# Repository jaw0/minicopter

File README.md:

teeny-tiny autonomous quadcopter flying machine

* 25mm square (smaller than one inch!)

* STM32F4 - ARM Cortex-M4

* 10 DOF IMU
  * accelerometer
  * gyro
  * magnetometer
  * barometer

* 3D printed frame

* buggy, poorly performing software

* see also: [hackaday.io](https://hackaday.io/project/7947-quadcopter-in-one-inch)

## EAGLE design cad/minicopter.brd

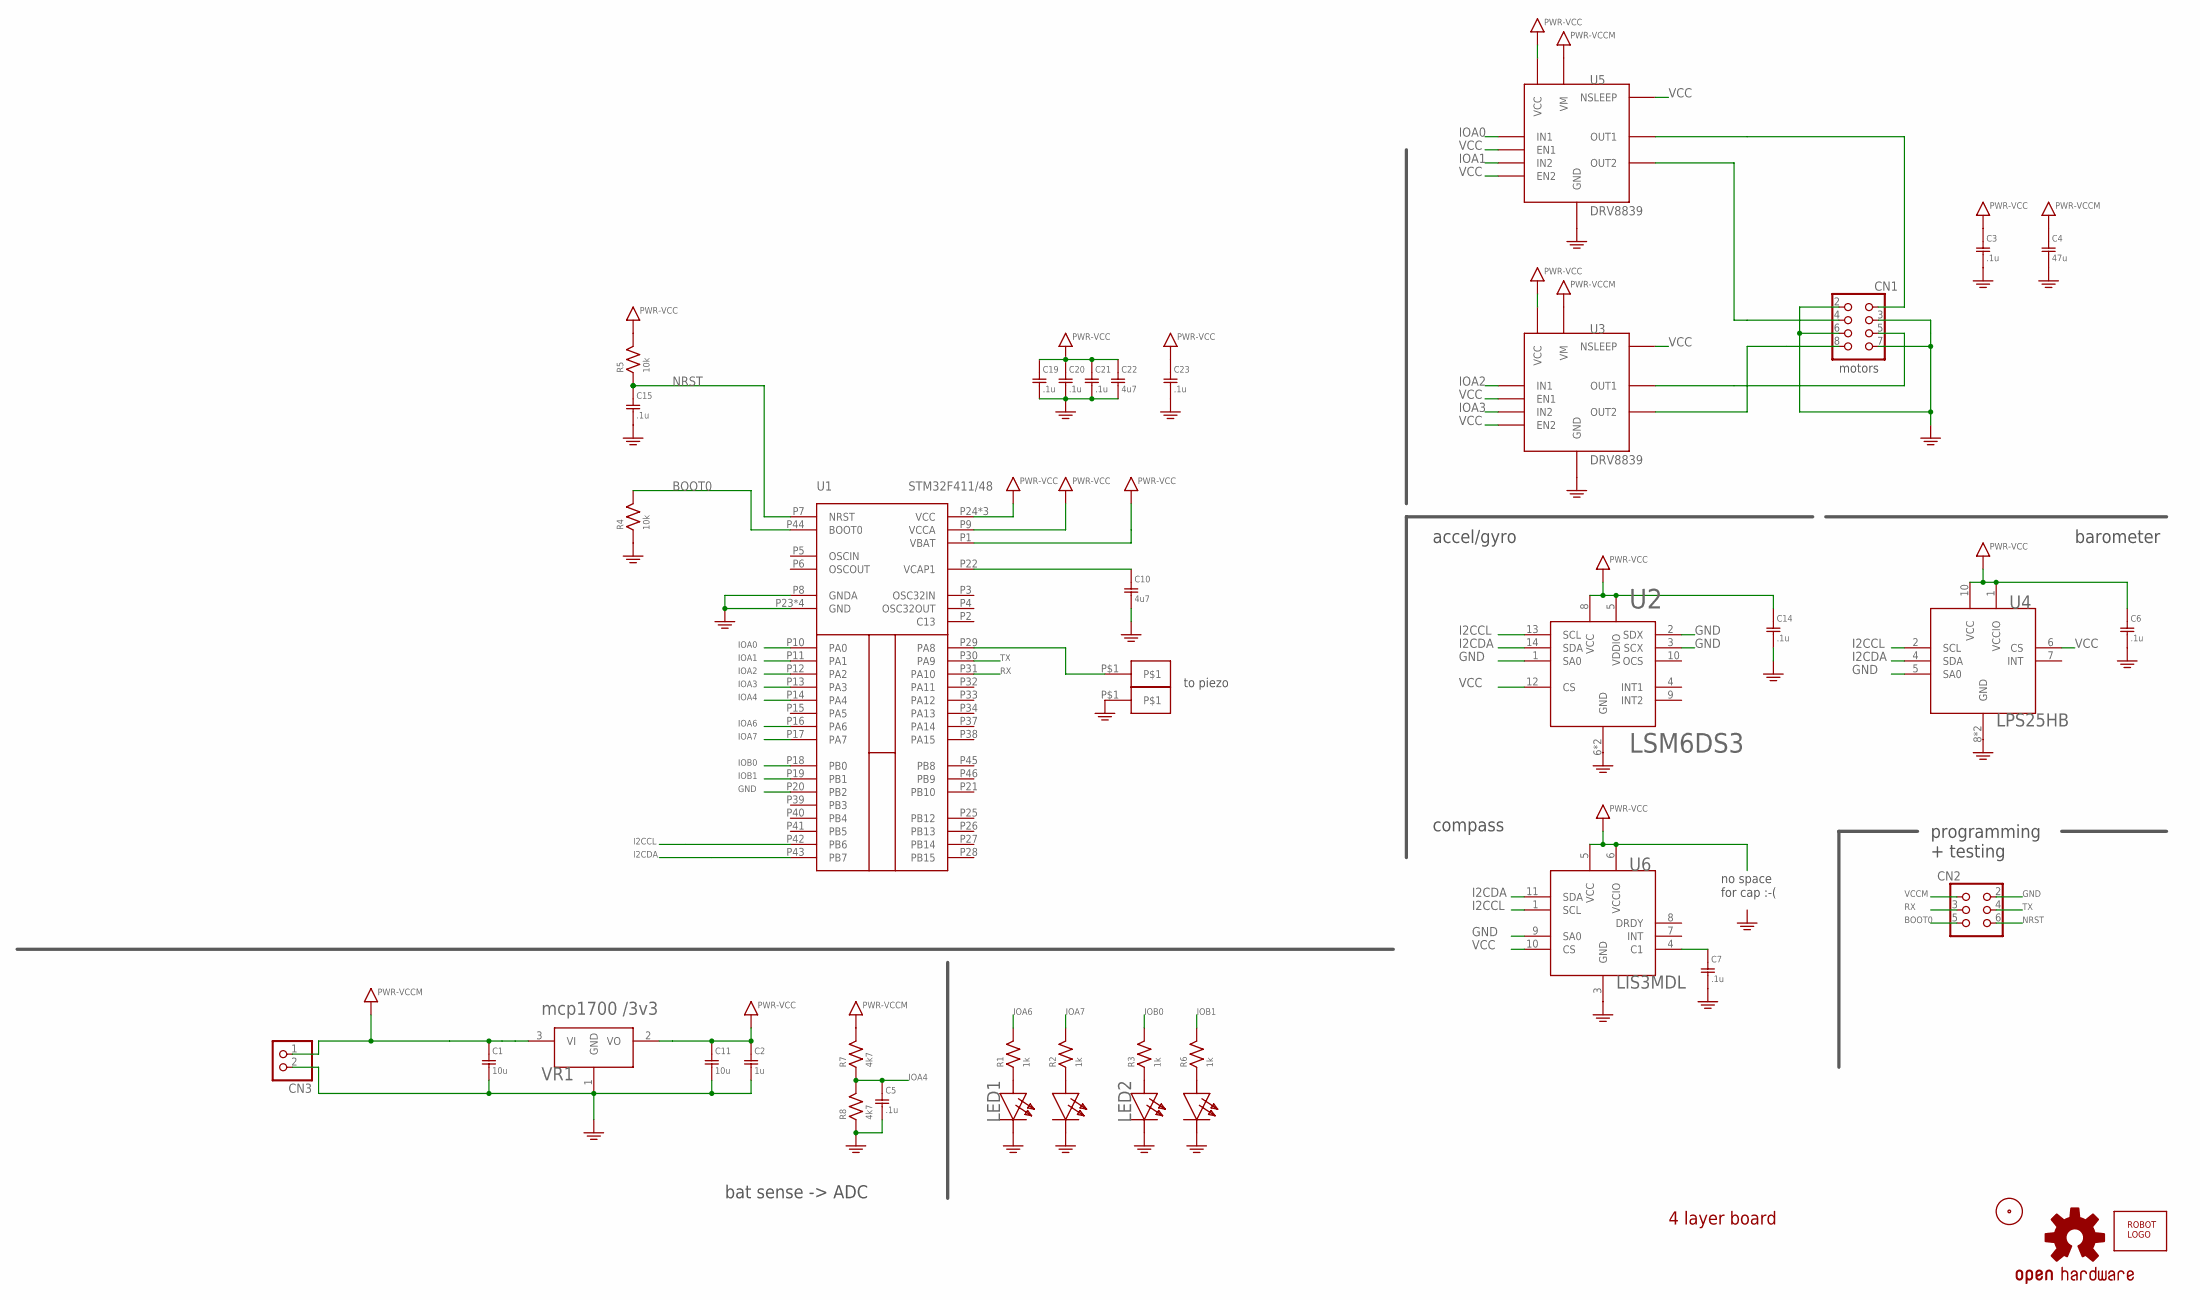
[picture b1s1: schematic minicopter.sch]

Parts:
C1, C11: 10u; SMD0603
C2: 1u; SMD0603
C3, C5, C6, C7, C14, C15, C19, C20, C21, C23: .1u; SMD0603
C4: 47u; SMD0805
C10, C22: 4u7; SMD0603
CN1: HEADER-2X4; HEADER-2X04-THM
CN2: HEADER-3X2-PTH
CN3: JST_2PIN-THM; JST-PH-2-THM
CN4, CN5: HEADER-1X1SMALL; HEADER-1X1-SMALL
LED1, LED2: LED-DUAL0805; SMD0805-DUAL
LOGO1: OSHW-LOGOM; OSHW-LOGO-M
R1, R2, R3, R6: 1k; SMD0603
R4, R5: 10k; SMD0603
R7, R8: 4k7; SMD0603
U1: STM32F411/48; UQPFN48
U2: LSM6DS3; LGA14A
U3, U5: DRV8839; WSON12
U4: LPS25HB; HLGA10L
U6: LIS3MDL; LGA12
U$1: ROBOTMAN-LOGO
U$2: FIDUCIAL
VR1: mcp1700 /3v3; SOT-23-3

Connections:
BOOT0: CN2.5, R4.2, U1.P44 (BOOT0)
GND: C1.2, C2.2, C3.2, C4.2, C5.2, C6.2, C7.2, C10.2, C11.2, C14.2, C15.2, C19.2, C20.2, C21.2, C22.2, C23.2, CN1.2, CN1.3, CN1.6, CN1.7, CN2.2, CN3.2 (1), CN5.P$1, LED1.2 (CB), LED1.3 (CR), LED2.2 (CB), LED2.3 (CR), R4.1, R8.1, U1.P8 (GNDA), U1.P20 (PB2), U1.P23 (GND), U1.P35 (GND), U1.P47 (GND), U1.PAD (GND), U2.1 (SA0), U2.2 (SDX), U2.3 (SCX), U2.6 (GND), U2.7 (GND), U3.5 (GND), U3.6 (GND), U3.GND3 (GND), U3.GND4 (GND), U3.GND5 (GND), U3.GND6 (GND), U3.GND7 (GND), U4.5 (SA0), U4.8 (GND), U4.9 (GND), U5.5 (GND), U5.6 (GND), U5.GND3 (GND), U5.GND4 (GND), U5.GND5 (GND), U5.GND6 (GND), U5.GND7 (GND), U6.3 (GND), U6.9 (SA0), VR1.1 (GND)
I2CCL: U1.P42 (PB6), U2.13 (SCL), U4.2 (SCL), U6.1 (SCL)
I2CDA: U1.P43 (PB7), U2.14 (SDA), U4.4 (SDA), U6.11 (SDA)
IOA0: U1.P10 (PA0), U5.10 (IN1)
IOA1: U1.P11 (PA1), U5.8 (IN2)
IOA2: U1.P12 (PA2), U3.10 (IN1)
IOA3: U1.P13 (PA3), U3.8 (IN2)
IOA4: C5.1, R7.1, R8.2, U1.P14 (PA4)
IOA6: R1.2, U1.P16 (PA6)
IOA7: R2.2, U1.P17 (PA7)
IOB0: R3.2, U1.P18 (PB0)
IOB1: R6.2, U1.P19 (PB1)
unnamed: LED1.1 (AB), R1.1
unnamed: LED1.4 (AR), R2.1
unnamed: LED2.1 (AB), R3.1
unnamed: LED2.4 (AR), R6.1
unnamed: CN1.1, U5.3 (OUT1)
unnamed: CN1.4, U5.4 (OUT2)
unnamed: C10.1, U1.P22 (VCAP1)
unnamed: CN1.5, U3.3 (OUT1)
unnamed: CN1.8, U3.4 (OUT2)
unnamed: C7.1, U6.4 (C1)
NRST: C15.1, CN2.6, R5.1, U1.P7 (NRST)
PZ0: CN4.P$1, U1.P29 (PA8)
RX: CN2.3, U1.P31 (PA10)
TX: CN2.4, U1.P30 (PA9)
VCC: C2.1, C3.1, C6.1, C11.1, C14.1, C19.1, C20.1, C21.1, C22.1, C23.1, R5.2, U1.P1 (VBAT), U1.P9 (VCCA), U1.P24 (VCC), U1.P36 (VCC), U1.P48 (VCC), U2.5 (VDDIO), U2.8 (VCC), U2.12 (CS), U3.7 (EN2), U3.9 (EN1), U3.11 (NSLEEP), U3.12 (VCC), U4.1 (VCCIO), U4.6 (CS), U4.10 (VCC), U5.7 (EN2), U5.9 (EN1), U5.11 (NSLEEP), U5.12 (VCC), U6.5 (VCC), U6.6 (VCCIO), U6.10 (CS), VR1.2 (VO)
VCCM: C1.1, C4.1, CN2.1, CN3.1 (2), R7.2, U3.1 (VM), U3.2 (VM), U5.1 (VM), U5.2 (VM), VR1.3 (VI)

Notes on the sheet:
programming + testing
bat sense -> ADC
motors
to piezo
no space for cap :-(
accel/gyro
compass
barometer
4 layer board

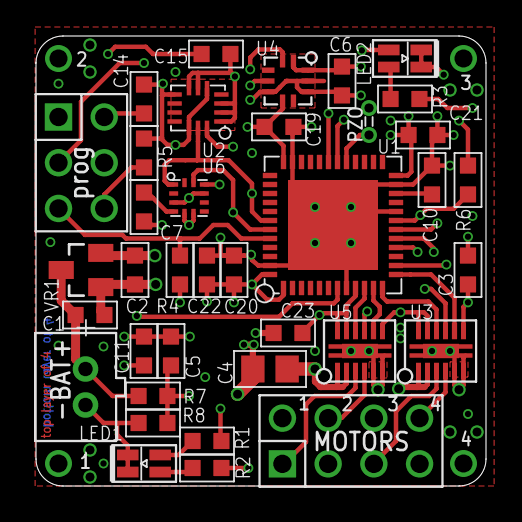
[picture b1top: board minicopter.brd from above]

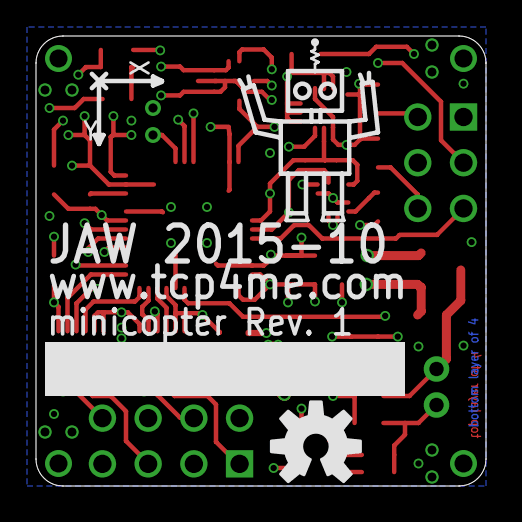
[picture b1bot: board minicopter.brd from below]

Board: 4 copper layers, 25.0 x 25.0 mm, 41 parts (2 on the bottom side), 29 nets.

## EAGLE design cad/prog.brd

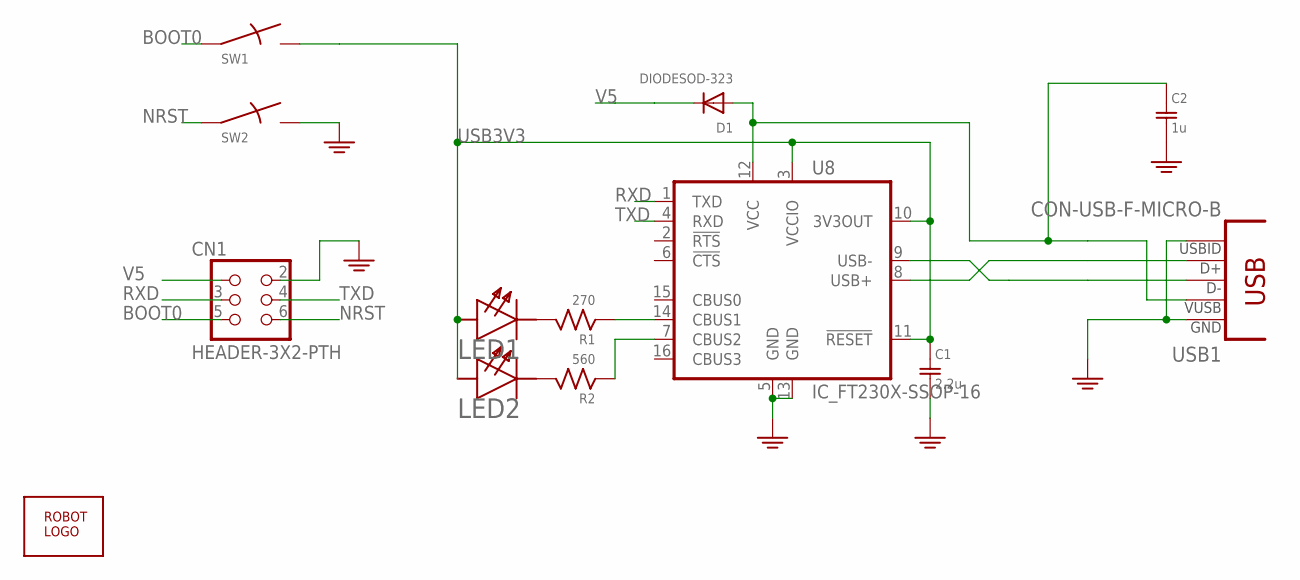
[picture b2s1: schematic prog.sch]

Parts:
C1: 2.2u; SMD0603
C2: 1u; SMD0603
CN1: HEADER-3X2-PTH
D1: DIODESOD-323; SOD-323
LED1: GREEN; SMD0603D
LED2: ORANGE; SMD0603D
R1: 270; SMD0603
R2: 560; SMD0603
SW1, SW2: SWITCHKMR211; KMR211
U8: IC_FT230X-SSOP-16; SSOP-16-FTDI
U$1: ROBOTMAN-LOGO
USB1: CON-USB-F-MICRO-B; CONN_USB_MICRO-B

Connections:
BOOT0: CN1.5, SW1.1, SW1.3
GND: C1.2, C2.2, CN1.2, SW2.2, SW2.4, U8.5 (GND), U8.13 (GND), USB1.P4 (USBID), USB1.P5 (GND)
unnamed: U8.8 (USB+), USB1.P3 (D+)
unnamed: U8.9 (USB-), USB1.P2 (D-)
unnamed: LED1.C, R1.2
unnamed: LED2.C, R2.2
unnamed: R1.1, U8.14 (CBUS1)
unnamed: R2.1, U8.7 (CBUS2)
NRST: CN1.6, SW2.1, SW2.3
RXD: CN1.3, U8.1 (TXD)
TXD: CN1.4, U8.4 (RXD)
USB3V3: C1.1, LED1.A, LED2.A, SW1.2, SW1.4, U8.3 (VCCIO), U8.10 (3V3OUT), U8.11 (!RESET)
V5: CN1.1, D1.C
VBUS: C2.1, D1.A, U8.12 (VCC), USB1.P1 (VUSB)

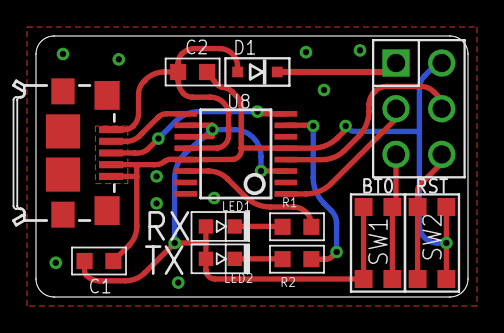
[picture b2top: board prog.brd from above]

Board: 2 copper layers, 24.0 x 14.5 mm, 13 parts (1 on the bottom side), 14 nets.

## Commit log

2015-10-07 rough draft
2015-10-08 motor driver
2015-10-08 add magnetometer
2015-10-08 tweak
2015-10-09 add piezo
2015-10-13 frame
2015-11-10 sch -> pdf
2015-11-10 thicken frame
2015-11-10 add files
2015-11-10 add stl
2015-11-26 add buggy software
2015-11-26 gerber files
2015-11-28 add file
2015-11-28 add comment
2016-12-01 add images

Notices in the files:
parts and their libraries:
SparkFun-Aesthetics: Licensing: Creative Commons ShareAlike 4.0 International - https://creativecommons.org/licenses/by-sa/4.0
